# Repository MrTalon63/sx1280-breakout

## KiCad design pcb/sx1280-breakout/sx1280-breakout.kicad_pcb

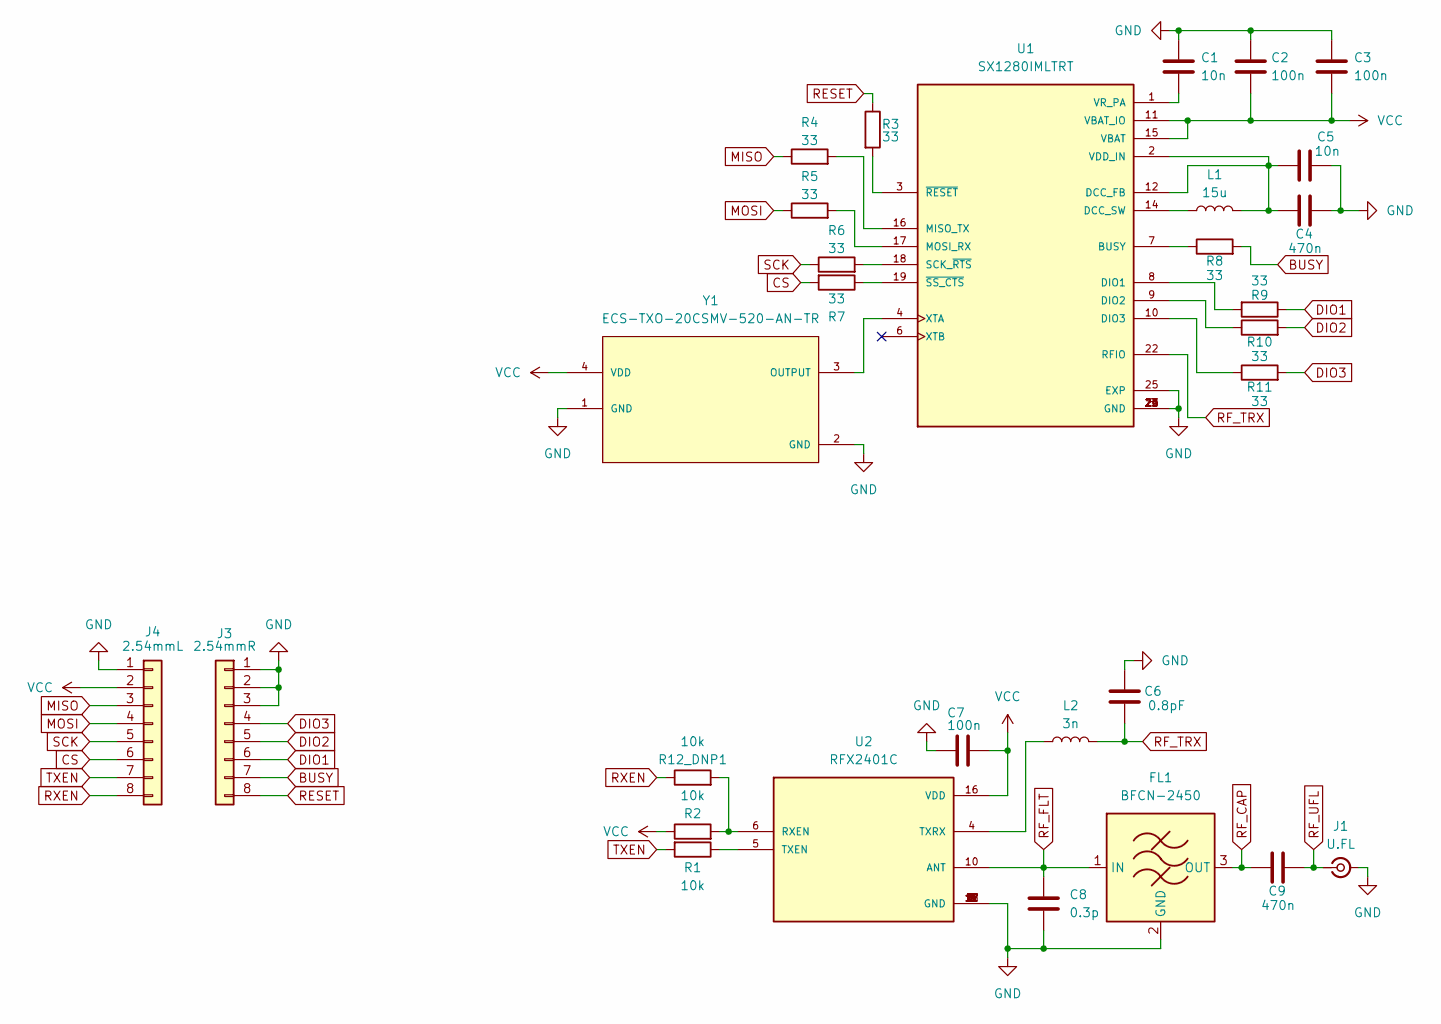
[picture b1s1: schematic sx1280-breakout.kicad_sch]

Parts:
C1, C5: 10n; C_0603_1608Metric
C2, C3, C7: 100n; C_0603_1608Metric
C4: 470n; C_0603_1608Metric
C6: 0.8pF; C_0402_1005Metric
C8: 0.3p; C_0402_1005Metric
C9: 470n; C_0402_1005Metric
FL1: BFCN-2450; Filter_Mini-Circuits_FV1206-4
J1: U.FL; U.FL_Molex_MCRF_73412-0110_Vertical
J3: 2.54mmR; PinHeader_1x08_P2.54mm_Vertical
J4: 2.54mmL; PinHeader_1x08_P2.54mm_Vertical
L1: 15u; L_0805_2012Metric
L2: 3n; L_0402_1005Metric
R1, R2, R12_DNP1: 10k; R_0402_1005Metric
R3, R4, R5, R6, R7, R8, R9, R10, R11: 33; R_0603_1608Metric
U1: SX1280IMLTRT; XCVR_SX1280IMLTRT; PARTREV 3.3
U2: RFX2401C
Y1: ECS-TXO-20CSMV-520-AN-TR; OSC_ECS-TXO-20CSMV-520-AN-TR

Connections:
BUSY: J3.7, R8.2
CS: J4.6, R7.2
DIO1: J3.6, R9.1
DIO2: J3.5, R10.2
DIO3: J3.4, R11.2
GND: C1.1, C2.1, C3.1, C4.2, C5.2, C6.2, C7.2, C8.2, FL1.2 (GND), FL1.4 (GND), J1.2 (Ext), J3.1, J3.2, J3.3, J4.1, U1.5 (GND), U1.13 (GND), U1.20 (GND), U1.21 (GND), U1.23 (GND), U1.24 (GND), U1.25 (EXP), U2.1 (GND), U2.2 (GND), U2.3 (GND), U2.7 (GND), U2.8 (GND), U2.9 (GND), U2.11 (GND), U2.12 (GND), U2.15 (GND), U2.17 (GND), Y1.1 (GND), Y1.2 (GND)
MISO: J4.3, R4.1
MOSI: J4.4, R5.1
unnamed: R8.1, U1.7 (BUSY)
unnamed: C4.1, C5.1, L1.2, U1.2 (VDD_IN), U1.12 (DCC_FB)
unnamed: L1.1, U1.14 (DCC_SW)
unnamed: R9.2, U1.8 (DIO1)
unnamed: R10.1, U1.9 (DIO2)
unnamed: R11.1, U1.10 (DIO3)
unnamed: R4.2, U1.16 (MISO_TX)
unnamed: R5.2, U1.17 (MOSI_RX)
unnamed: R6.2, U1.18 (SCK_~RTS)
unnamed: C1.2, U1.1 (VR_PA)
unnamed: U1.4 (XTA), Y1.3 (OUTPUT)
unnamed: R3.2, U1.3 (~RESET)
unnamed: R7.1, U1.19 (~SS_CTS)
unnamed: R2.2, R12_DNP1.2, U2.6 (RXEN)
unnamed: R1.1, U2.5 (TXEN)
unnamed: L2.1, U2.4 (TXRX)
RESET: J3.8, R3.1
RF_CAP: C9.1, FL1.3 (OUT)
RF_FLT: C8.1, FL1.1 (IN), U2.10 (ANT)
RF_TRX: C6.1, L2.2, U1.22 (RFIO)
RF_UFL: C9.2, J1.1 (In)
RXEN: J4.8, R12_DNP1.1
SCK: J4.5, R6.1
TXEN: J4.7, R1.2
VCC: C2.2, C3.2, C7.1, J4.2, R2.1, U1.11 (VBAT_IO), U1.15 (VBAT), U2.16 (VDD), Y1.4 (VDD)

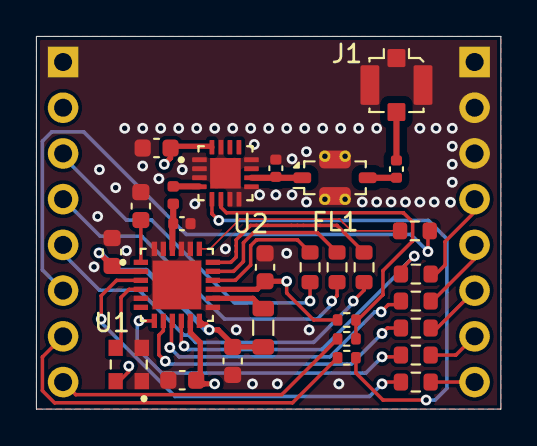
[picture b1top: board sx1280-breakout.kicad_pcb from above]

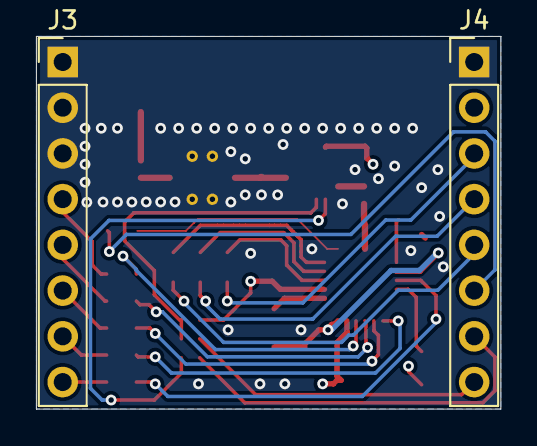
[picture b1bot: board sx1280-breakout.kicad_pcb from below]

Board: 4 copper layers, 25.8 x 20.7 mm, 30 parts (2 on the bottom side), 33 nets.

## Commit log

2025-03-25 Initial design
